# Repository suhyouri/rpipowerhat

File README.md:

# rpipowerhat

##Eagle Library 

DC-DC Converter 

12V to 5V

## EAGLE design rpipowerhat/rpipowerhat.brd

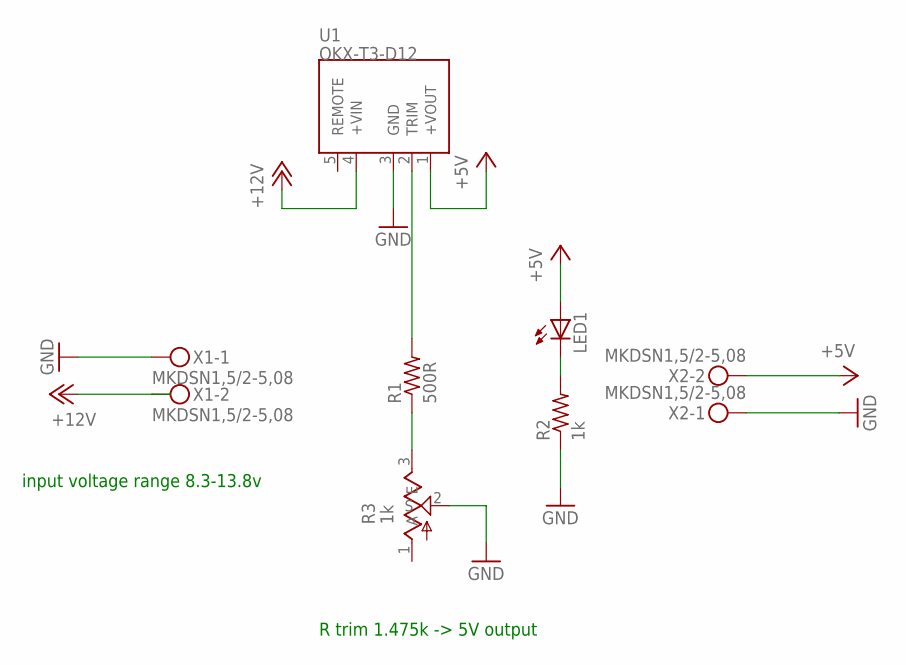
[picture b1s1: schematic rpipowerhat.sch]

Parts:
LED1: LEDCHIPLED_0603; CHIPLED_0603
R1: 500R; R0603
R2: 1k; R0603
R3: 1k; RTRIM3296W
U1: OKX-T3-D12
X1, X2: MKDSN1,5/2-5,08

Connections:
+5V: LED1.A, U1.1 (+VOUT), X2.2
+12V: U1.4 (+VIN), X1.2
GND: R2.1, R3.2 (S), U1.3 (GND), X1.1, X2.1
unnamed: R1.1, R3.3 (E)
unnamed: R1.2, U1.2 (TRIM)
unnamed: LED1.C, R2.2

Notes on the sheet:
R trim 1.475k -> 5V output
input voltage range 8.3-13.8v

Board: 2 copper layers, 7 parts (0 on the bottom side), 6 nets, no tracks yet.

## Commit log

2021-04-18 setting
2021-04-18 add device
2021-04-23 homework done
